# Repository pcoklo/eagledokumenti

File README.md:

eagledokumenti
==============

nešto što crtam i šeram

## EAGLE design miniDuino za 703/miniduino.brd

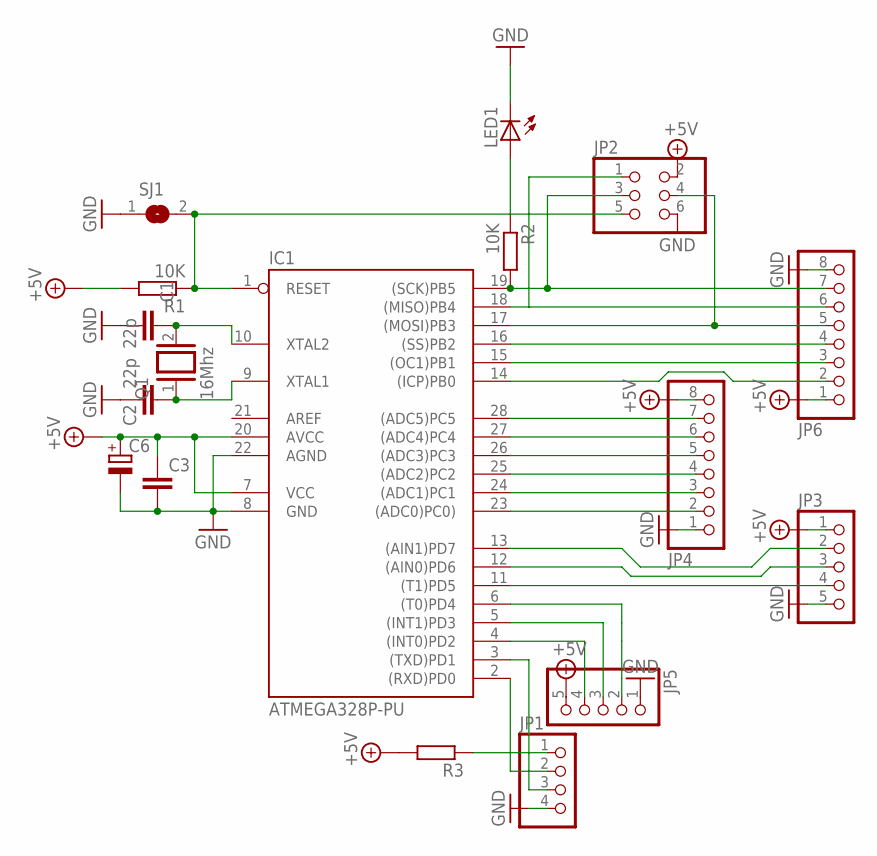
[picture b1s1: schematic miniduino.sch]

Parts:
C1, C2: 22p; C025-024X044
C3: C-EU050-025X075; C050-025X075
C6: CPOL-EUE2.5-5; E2,5-5
IC1: ATMEGA328P-PU; DIL28-3
JP1: PINHD-1X4; 1X04
JP2: PINHD-2X3; 2X03
JP3, JP5: PINHD-1X5; 1X05
JP4, JP6: PINHD-1X8; 1X08
LED1: LED3MM
Q1: 16Mhz; QS
R1, R2: 10K; 0204V
R3: R-EU_0204/2V; 0204V
SJ1: SJ

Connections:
+5V: C3.1, C6.+, IC1.7 (VCC), IC1.20 (AVCC), JP2.2, JP3.1, JP4.8, JP5.5, JP6.1, R1.2, R3.2
GND: C1.2, C2.1, C3.2, C6.-, IC1.8 (GND), IC1.22 (AGND), JP1.4, JP2.6, JP3.5, JP4.1, JP5.1, JP6.8, LED1.K (C), SJ1.1
unnamed: C1.1, IC1.10 (XTAL2), Q1.2
unnamed: IC1.2 ((RXD)PD0), JP1.2
unnamed: IC1.3 ((TXD)PD1), JP1.3
unnamed: C2.2, IC1.9 (XTAL1), Q1.1
unnamed: IC1.1 (RESET), JP2.5, R1.1, SJ1.2
unnamed: LED1.A, R2.1
unnamed: IC1.11 ((T1)PD5), JP3.4
unnamed: IC1.12 ((AIN0)PD6), JP3.3
unnamed: IC1.19 ((SCK)PB5), JP2.3, JP6.7, R2.2
unnamed: IC1.13 ((AIN1)PD7), JP3.2
unnamed: IC1.14 ((ICP)PB0), JP6.2
unnamed: IC1.15 ((OC1)PB1), JP6.3
unnamed: IC1.16 ((SS)PB2), JP6.4
unnamed: IC1.23 ((ADC0)PC0)), JP4.2
unnamed: IC1.24 ((ADC1)PC1), JP4.3
unnamed: IC1.25 ((ADC2)PC2), JP4.4
unnamed: IC1.26 ((ADC3)PC3), JP4.5
unnamed: IC1.27 ((ADC4)PC4), JP4.6
unnamed: IC1.28 ((ADC5)PC5), JP4.7
unnamed: IC1.6 ((T0)PD4), JP5.2
unnamed: IC1.5 ((INT1)PD3), JP5.3
unnamed: IC1.4 ((INT0)PD2), JP5.4
unnamed: JP1.1, R3.1
unnamed: IC1.17 ((MOSI)PB3), JP2.4, JP6.5
unnamed: IC1.18 ((MISO)PB4), JP2.1, JP6.6

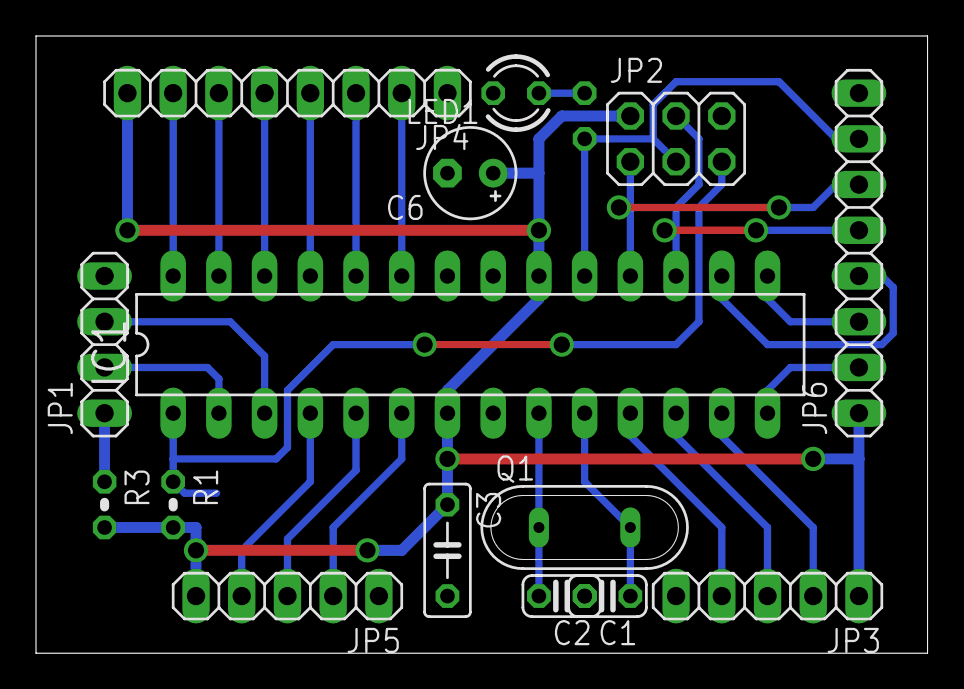
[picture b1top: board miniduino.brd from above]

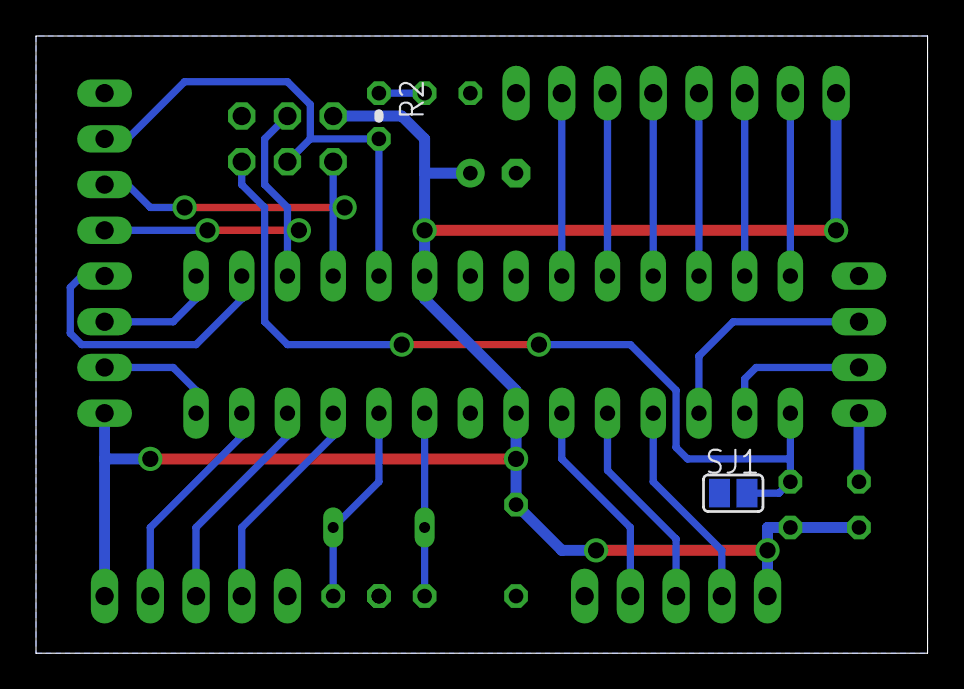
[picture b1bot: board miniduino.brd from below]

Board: 2 copper layers, 49.5 x 34.3 mm, 17 parts (2 on the bottom side), 27 nets.

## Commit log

2013-08-13 mali arduino
